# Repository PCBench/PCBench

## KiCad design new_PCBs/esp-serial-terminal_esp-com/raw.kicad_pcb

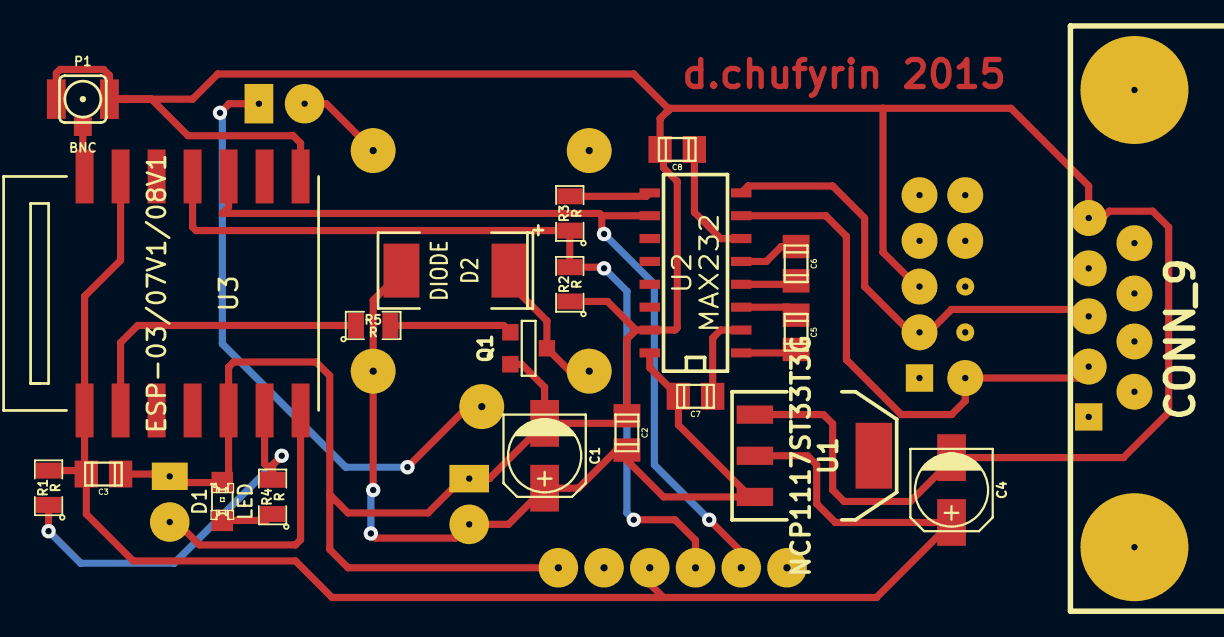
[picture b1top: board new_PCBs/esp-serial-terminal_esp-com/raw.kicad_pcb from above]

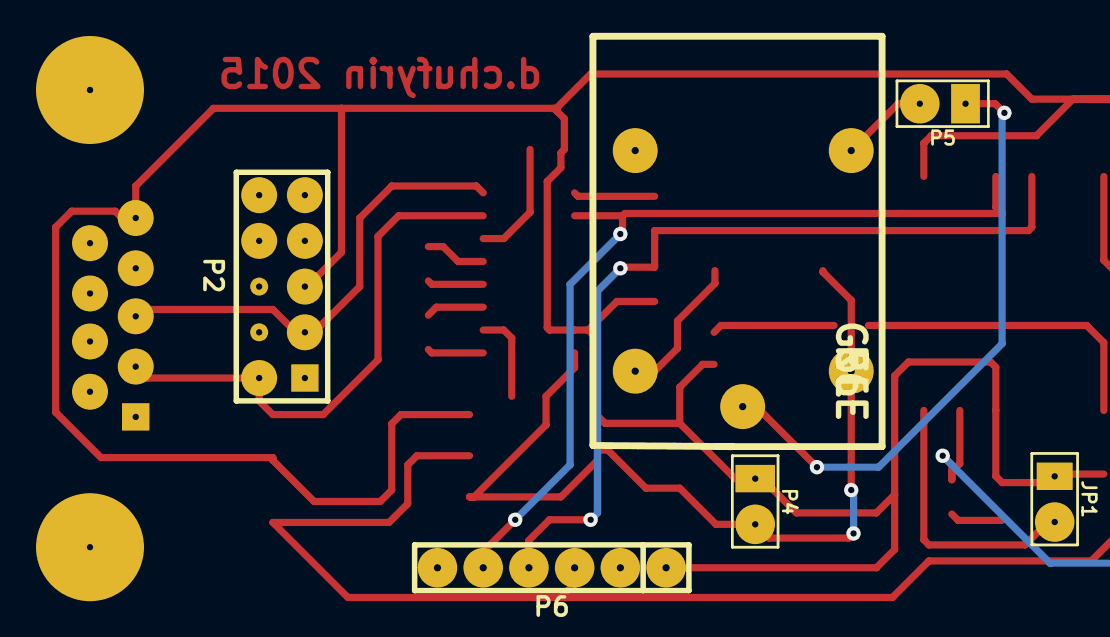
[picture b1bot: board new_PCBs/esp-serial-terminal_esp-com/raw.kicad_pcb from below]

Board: 2 copper layers, 27 parts (6 on the bottom side), 22 nets.

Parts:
C1: CP1; c_elec_4x5.8
C2, C3, C5, C6, C7, C8: C; c_0805
C4: CP1; c_elec_4x5.7
D1: LED; LED-0805
D2: DIODE; SM2512
JP1: JUMPER; PIN_ARRAY_2X1
P1: BNC; coaxial_u.fl-r-smt-1
P2: CONN_5X2; PIN_ARRAY_5x2
P3: CONN_9; DB9MC
P4, P5: CONN_2; PIN_ARRAY_2X1
P6: CONN_6; PIN_ARRAY-6X1
Q1: NPN; SOT23EBC
R1, R2, R3, R4, R5: R; SM0805
R6: G5LE
U1: NCP1117ST33T3G; SOT223
U2: MAX232; SO16E
U3: ESP-03/07V1/08V1; ESP-03

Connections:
+5V: C1.1, C2.1, C7.1, D2.2, P4.2, R6.2, U1.3, U2.16
GND: C1.2, C2.2, C3.2, C4.2, C8.1, D1.2, JP1.1, JP1.2, P1.2, P2.5, P3.5, P4.1, P6.1, Q1.1, R2.1, U1.1, U2.15, U3.5, U3.7, U3.8
unnamed: P2.2, P3.2, U2.7
unnamed: P2.3, P3.3, U2.8
unnamed: D2.1, Q1.3, R6.1
unnamed: C7.2, U2.2
unnamed: C8.2, U2.6
unnamed: C5.2, U2.3
unnamed: C5.1, U2.1
unnamed: C6.1, U2.4
unnamed: C6.2, U2.5
unnamed: R3.2, U2.9
unnamed: P6.4, R2.2, R3.1, U3.11
unnamed: P1.1, U3.14
unnamed: R5.1, U3.2
unnamed: D1.1, R4.1
unnamed: Q1.2, R5.2
unnamed: P5.2, R6.5
unnamed: P5.1, R6.4
unnamed: P6.5, U2.10, U3.10
unnamed: R1.1, R4.2, U3.6
unnamed: C3.1, C4.1, P6.3, R1.2, U1.2, U3.1, U3.13

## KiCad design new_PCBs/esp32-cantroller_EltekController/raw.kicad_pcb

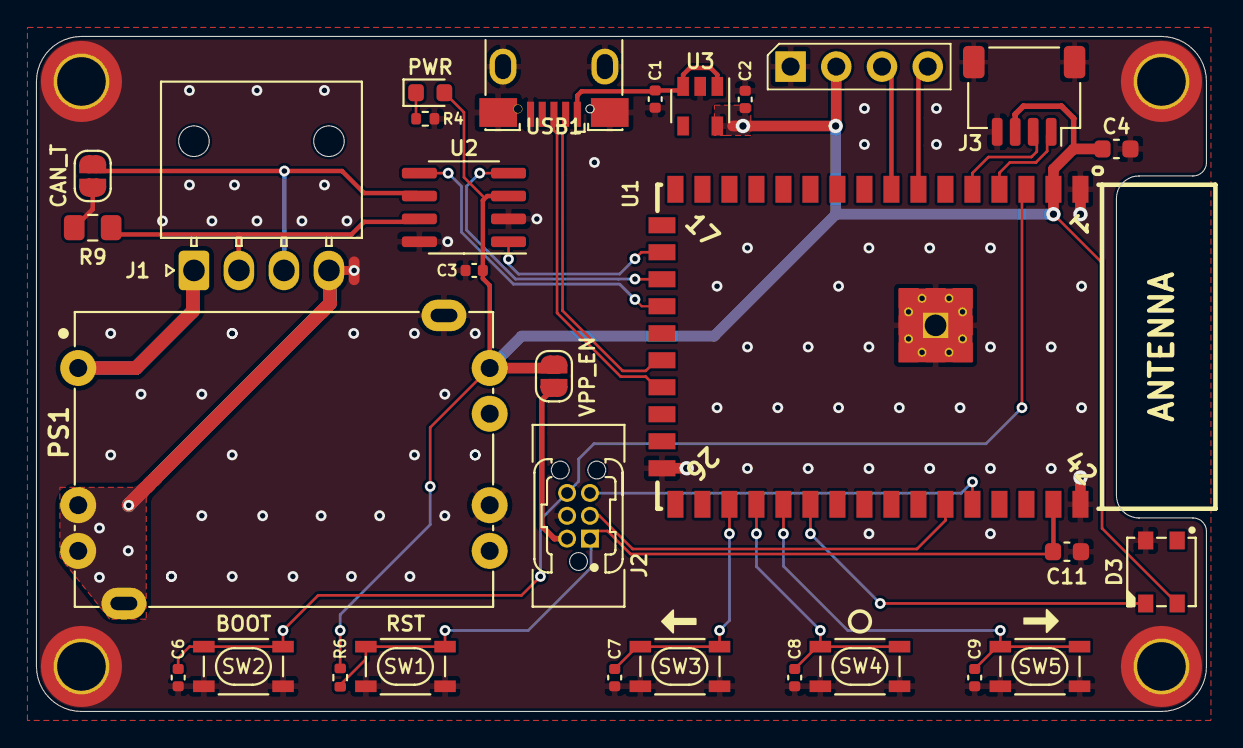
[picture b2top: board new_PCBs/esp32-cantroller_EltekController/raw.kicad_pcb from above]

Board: 2 copper layers, 65.0 x 37.5 mm, 36 parts (1 on the bottom side), 27 nets.

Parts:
C1, C2, C3: 10uF; C_0402_1005Metric
C4: 22uF; C_0603_1608Metric
C6, C7, C8, C9: 100nF; C_0402_1005Metric
C11: 10uF; C_0603_1608Metric
D2: PWR; LED_0603_1608Metric_SnapModel
D3: SK6812MINI; LED_SK6812MINI_PLCC4_3.5x3.5mm_P1.75mm_3D
H1, H2, H3, H4: MP; MountingHole_2.7mm_M2.5_ISO7380_Pad_TopBottom
I2C1: OLED; OLED_SSD1315_128x64_1.3_I2C_New_Silhouette_Big3D
J1: CANBUS; Molex_Nano-Fit_105313-xx04_1x04_P2.50mm_Horizontal_3D
J2: ESP-PROG; Gecko-G125_PlusTC2030_IDCBox_2x03_P1.25mm_Vertical_3D
J3: Qwiic; JST_SH_SM04B-SRSS-TB_1x04-1MP_P1.00mm_Horizontal_3D
JP1: VPP_EN; SolderJumper-2_P1.3mm_Open_RoundedPad1.0x1.5mm
JP2: CAN_T; SolderJumper-2_P1.3mm_Open_RoundedPad1.0x1.5mm
LOGO1: Logo_Open_Hardware_Small; neggle-logo-0.12
NT1: GND_TIE; NetTie-2_SMD_Pad0.5mm
PS1: CC3-4803SF-E; Converter_DCDC_TDK-Lambda_CC3-xxxxxF-E
R4: 1K; R_0402_1005Metric
R6: 10K; R_0402_1005Metric
R9: 120R; R_0805_2012Metric_Pad1.15x1.40mm_HandSolder
SW1: RST; KEY-SMD_4P-L4.2-W3.2-P2.20-LS5.1-TL
SW2: BOOT; KEY-SMD_4P-L4.2-W3.2-P2.20-LS5.1-TL
SW3: LEFT; KEY-SMD_4P-L4.2-W3.2-P2.20-LS5.1-TL
SW4: SEL; KEY-SMD_4P-L4.2-W3.2-P2.20-LS5.1-TL
SW5: RIGHT; KEY-SMD_4P-L4.2-W3.2-P2.20-LS5.1-TL
U1: ESP32-S2-WROVER; ESP32-S2-WROVER_and_WROOM(PCB,-I(IPEX))-Universal
U2: MAX3051ESA; SOIC-8_3.9x4.9mm_P1.27mm
U3: XC6220B331MR; SOT-23-5
USB1: USB; MICRO-USB-SMD_U254-051T-4BH83-F1S_C397452

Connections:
+3V3: C2.2, C3.2, C4.2, D2.2, D3.4, I2C1.2, J3.3, JP1.1, PS1.7, R6.2, U1.2, U2.3, U3.5
+48V: J1.1, PS1.1
/CAN+: J1.2, R9.1, U2.7
/CAN-: J1.3, JP2.2, U2.6
/CAN_RX: U1.19, U2.4
/CAN_TX: U1.18, U2.1
/LED_D: D3.3, U1.32
/OLED_SCL: I2C1.3, U1.8
/OLED_SDA: I2C1.4, U1.7
/QW_SCL: J3.1, U1.4
/QW_SDA: J3.2, U1.5
/U0RXD: J2.5, U1.38
/U0TXD: J2.3, U1.37
/USB_D+: U1.23, USB1.3
/USB_D-: U1.22, USB1.2
/VBUS: C1.2, U3.1, U3.3, USB1.1
/VPP: J2.2, JP1.2
/~BOOT: C6.2, J2.6, SW2.1, U1.3
/~CAN_EN: U1.20, U2.5
/~RST: C11.1, J2.1, R6.1, SW1.1, U1.41
/~SW_L: C7.2, SW3.1, U1.29
/~SW_R: C9.2, SW5.1, U1.31
/~SW_S: C8.2, SW4.1, U1.30
GND: C1.1, C2.1, C3.1, C4.1, C6.1, C7.1, C8.1, C9.1, C11.2, D3.2, H1.1, H2.1, H3.1, H4.1, I2C1.1, J2.4, J3.4, J3.MP, NT1.2, PS1.5, PS1.MP2, R4.1, SW1.2, SW2.2, SW3.2, SW4.2, SW5.2, U1.1, U1.26, U1.42, U1.43, U2.2, U2.8, U3.2, USB1.5, USB1.6
GNDPWR: J1.4, NT1.1, PS1.2, PS1.3, PS1.MP
unnamed: D2.1, R4.2
unnamed: JP2.1, R9.2

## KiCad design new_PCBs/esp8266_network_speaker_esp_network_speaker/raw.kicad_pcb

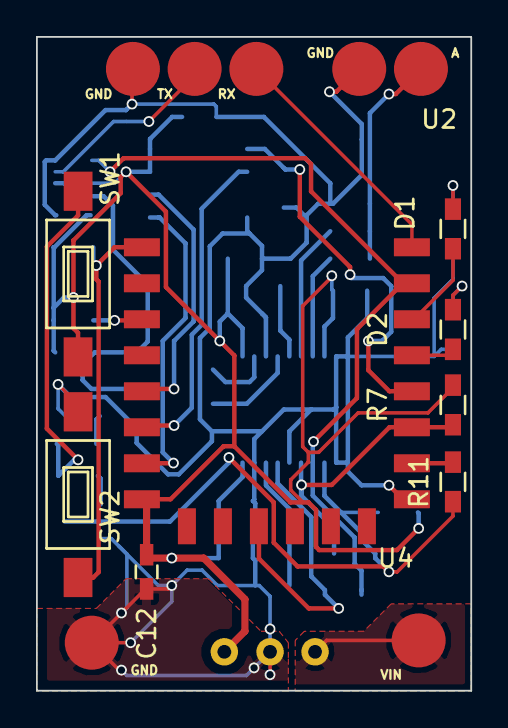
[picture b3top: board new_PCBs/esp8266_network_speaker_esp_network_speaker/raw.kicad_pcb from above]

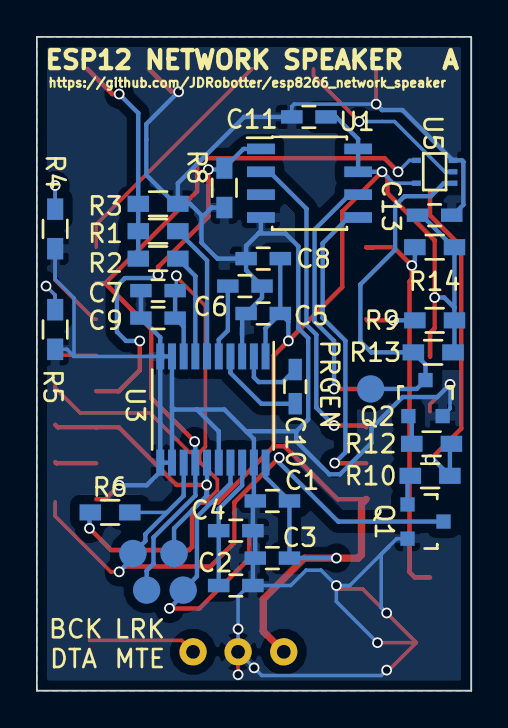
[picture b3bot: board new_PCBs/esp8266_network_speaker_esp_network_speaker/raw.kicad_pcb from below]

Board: 2 copper layers, 24.1 x 36.3 mm, 50 parts (34 on the bottom side), 31 nets.

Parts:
BCK: TEST_1P; Measurement_Point_Round-SMD-Pad_Small
C1, C2, C8, C9, C11, C12, C13: 100nF; C_0603_HandSoldering
C3, C4, C5, C7: 10uF; C_0603_HandSoldering
C6, C10: 2.2uF; C_0603_HandSoldering
D1, D2: LED; R_0603_HandSoldering
DTA: TEST_1P; Measurement_Point_Round-SMD-Pad_Small
LRK: TEST_1P; Measurement_Point_Round-SMD-Pad_Small
MTE: TEST_1P; Measurement_Point_Round-SMD-Pad_Small
PRGEN: TEST_1P; Measurement_Point_Round-SMD-Pad_Small
Q1, Q2: Q_NPN_BEC; SOT-23
R1, R2: 470; R_0603_HandSoldering
R3, R6, R7, R8, R9, R13, R14: 10k; R_0603_HandSoldering
R4, R5: 220; R_0603_HandSoldering
R10, R12: 1k; R_0603_HandSoldering
R11: 100; R_0603_HandSoldering
SW1, SW2: SW_PUSH; SW_SPST_FSMSM
U1: 23LC1024; SOIC-8_3.9x4.9mm_Pitch1.27mm
U2: ESP12
U3: PCM5100A; TSSOP-20_4.4x6.5mm_Pitch0.65mm
U4: TSR_1-2433; TSR-1
U5: M74VHC1GT125; SOT-353
W7: AOUT; Measurement_Point_Round-SMD-Pad_Big
W8: AGND; Measurement_Point_Round-SMD-Pad_Big
W9: PBATT; Measurement_Point_Round-SMD-Pad_Big
W10: PGND; Measurement_Point_Round-SMD-Pad_Big
W11: PROG_GND; Measurement_Point_Round-SMD-Pad_Big
W12: PROG_RX; Measurement_Point_Round-SMD-Pad_Big
W13: PROG_TX; Measurement_Point_Round-SMD-Pad_Big

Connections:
+3V3: C1.1, C3.1, C5.1, C7.1, C8.1, C9.1, C11.1, C12.1, C13.1, R6.1, R7.1, R9.2, R13.1, R14.1, SW1.1, U1.7, U1.8, U2.8, U3.1, U3.8, U3.20, U4.3, U5.5
/PROG_EN: PRGEN.1, Q2.3, R13.2, U5.1
/PROG_TX: U5.2, W13.1
/VBATT: U4.1, W9.1
DAC_BCK: BCK.1, Q1.3, R6.2, R11.1, U3.13
DAC_DATA: DTA.1, U2.21, U3.14, U5.4
DAC_LRCK: LRK.1, R7.2, U2.17, U3.15
DAC_MUTE: MTE.1, U2.11, U3.17
DAC_OUTL: R1.2, U3.6
DAC_OUTR: R2.2, U3.7
ESP12_CLK: U1.6, U2.5
ESP12_CS: R8.1, U1.1, U2.18
ESP12_MISO: U1.2, U2.6
ESP12_MOSI: U1.5, U2.7
ESP12_RESET: R14.2, SW2.1, U2.1
ESP12_TX: U2.22, W12.1
GND: C1.2, C2.1, C3.2, C4.2, C5.2, C6.1, C7.2, C8.2, C9.2, C11.2, C12.2, C13.2, Q1.2, Q2.2, R3.2, R4.1, R5.1, R8.2, SW2.2, U1.4, U2.15, U3.3, U3.9, U3.10, U3.11, U3.12, U3.16, U3.19, U4.2, U5.3, W8.1, W10.1, W11.1
LEDA: D2.2, U2.19
LEDB: D1.2, U2.20
unnamed: C2.2, C4.1, U3.18
unnamed: C6.2, U3.5
unnamed: C10.1, U3.2
unnamed: C10.2, U3.4
unnamed: D1.1, R4.2
unnamed: D2.1, R5.2
unnamed: Q1.1, R10.1
unnamed: Q2.1, R12.1
unnamed: R1.1, R2.1, R3.1, W7.1
unnamed: R9.1, U2.3
unnamed: R10.2, R12.2, SW1.2
unnamed: R11.2, U2.16

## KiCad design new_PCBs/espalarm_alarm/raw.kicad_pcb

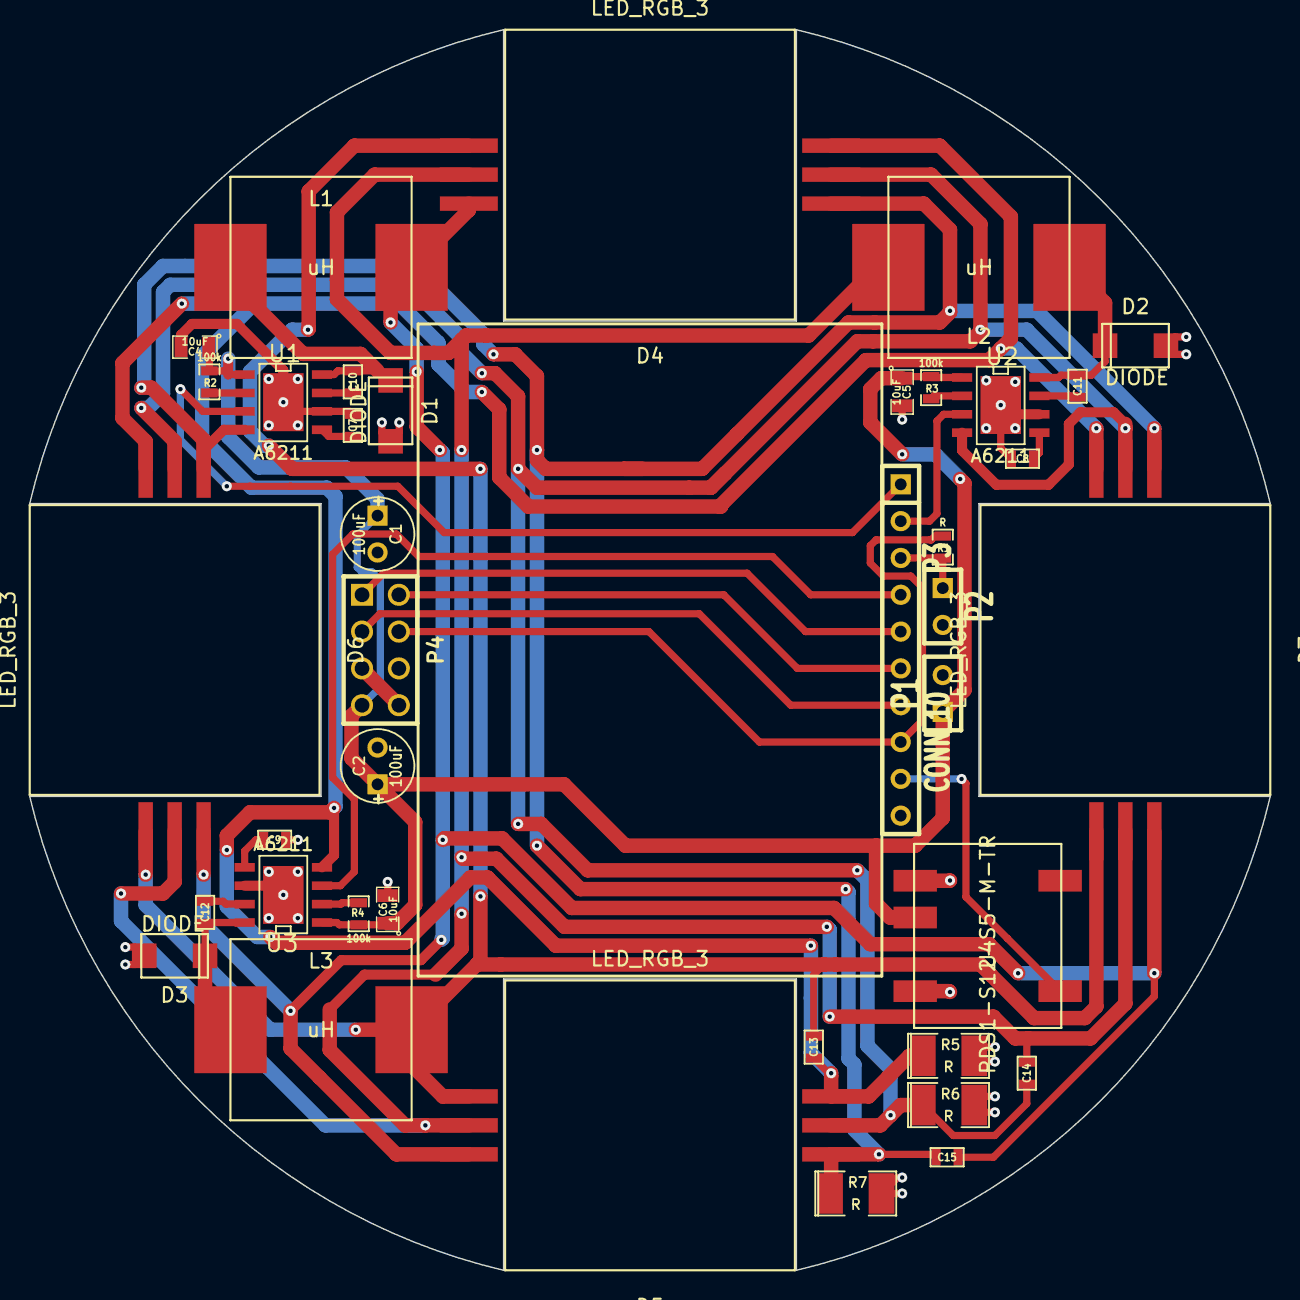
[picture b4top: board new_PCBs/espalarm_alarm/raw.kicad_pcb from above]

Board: 2 copper layers, 85.6 x 85.6 mm, 39 parts (0 on the bottom side), 29 nets.

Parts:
C1, C2: 100uF; C1V5
C4, C5, C6: 10uF; SM0805
C7, C8, C9, C10, C11, C12: 100nF; SM0603
C13, C14, C15: 1uF; SM0603
D1, D2, D3: DIODE; DIODE_SMA
D4, D5, D6, D7: LED_RGB_3; RGB_LED_10W
L1, L2, L3: uH; IND_12.5x12.5mm
P1, P2: CONN_2; SIL-2
P3: CONN_10; SIL-10
P4: CONN_8; pin_array_4x2
R1: R; SM0603_Resistor
R2, R3, R4: 100k; SM0603_Resistor
R5, R6, R7: R; SM1210L
U1, U2, U3: A6211; SO8_WITH_EP
U4: PDS1-S12-S5-M-TR

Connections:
/3.3V: P3.8, P4.4, R1.1
/5V: P3.9, U4.5
/12V: C1.1, C2.1, C4.1, C5.1, C6.1, P1.1, P4.7, R2.1, R3.1, R4.1, U1.1, U2.1, U3.1, U4.2
/GPIO0: P3.7, P4.3
/GPIO2: P3.6, P4.2
/GPIO12: P3.2, U2.3
/GPIO13: P3.4, U3.3
/GPIO14: P3.1, U1.3
/GPIO15: P3.5, P4.1
/GPIO16: P2.1, P3.3, R1.2
GND: C1.2, C2.2, C4.2, C5.2, C6.2, C7.2, C8.2, C9.2, D1.1, D2.1, D3.1, P1.2, P2.2, P3.10, P4.5, P4.8, R5.2, R6.2, R7.2, U1.6, U1.9, U2.6, U2.9, U3.6, U3.9, U4.1, U4.4
unnamed: C14.2, D4.5, D5.5, D6.5, D7.5, R6.1, U2.4
unnamed: C11.1, U2.7
unnamed: C11.2, D2.2, L2.1, U2.8
unnamed: R3.2, U2.2
unnamed: C9.1, U3.5
unnamed: R4.2, U3.2
unnamed: C8.1, U2.5
unnamed: C10.1, U1.7
unnamed: C10.2, D1.2, L1.1, U1.8
unnamed: C12.1, U3.7
unnamed: C12.2, D3.2, L3.1, U3.8
unnamed: C13.1, D4.1, D5.1, D6.1, D7.1, L3.2
unnamed: C7.1, U1.5
unnamed: C15.1, D4.3, D5.3, D6.3, D7.3, L1.2
unnamed: R2.2, U1.2
unnamed: C15.2, D4.4, D5.4, D6.4, D7.4, R7.1, U1.4
unnamed: C13.2, D4.6, D5.6, D6.6, D7.6, R5.1, U3.4
unnamed: C14.1, D4.2, D5.2, D6.2, D7.2, L2.2

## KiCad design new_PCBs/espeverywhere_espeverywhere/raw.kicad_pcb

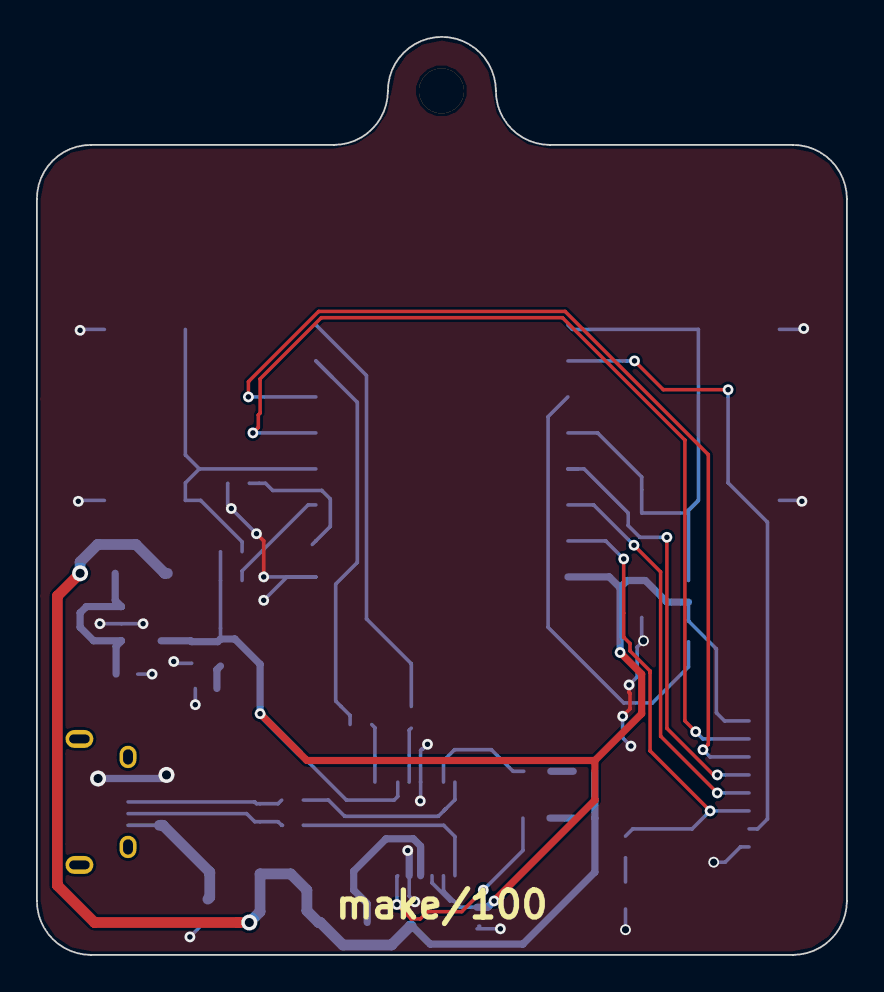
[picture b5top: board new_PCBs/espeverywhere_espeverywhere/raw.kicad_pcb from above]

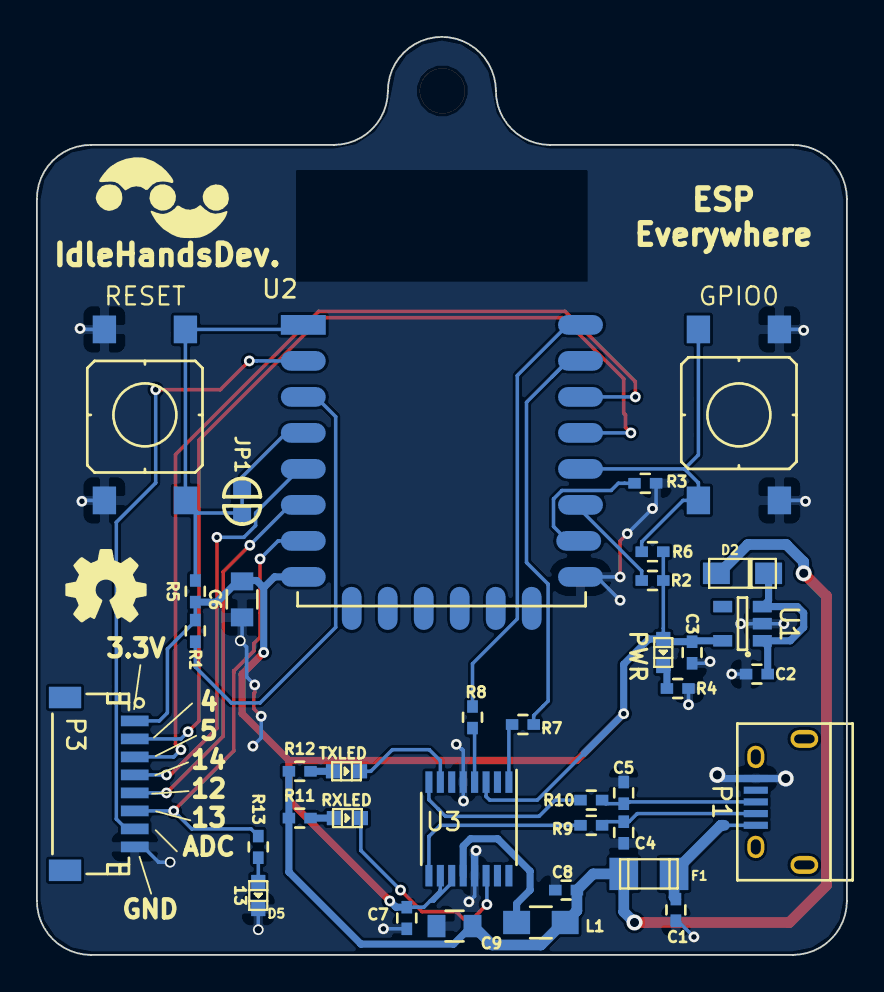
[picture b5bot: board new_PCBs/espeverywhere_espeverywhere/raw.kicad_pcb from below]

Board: 2 copper layers, 45.0 x 51.0 mm, 37 parts (37 on the bottom side), 31 nets.

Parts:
C1, C7, C8: 0.1uF; C_0402_Hand
C2: 1uF; C_0402_Hand
C3: 2.2uF; C_0402_Hand
C4, C5: 47pF; C_0402_Hand
C6, C9: 10uF; C_0805
D1: PWR; Led_0603
D2: BAT20J; bat20j
D3: RXLED; Led_0603
D4: TXLED; Led_0603
D5: 13; Led_0603
F1: 500mA; c_1206
JP1: Jumper_NC_Small; SOLDER-JUMPER_1-WAY-CLOSED
L1: FB; R_0805_HandSoldering
P1: USB_OTG; USB_Micro-B
P3: CONN_01X08; Connectors_JST_SM08B-SRSS-TB
R1, R2, R5: 10K; R_0402_Hand
R3, R4, R6, R7, R8, R11, R12, R13: 1K; R_0402_Hand
R9, R10: 27R; R_0402_Hand
SW2: GPIO0; Button_CKN9112CT-ND
SW3: RESET; Button_CKN9112CT-ND
U1: AP2112K-3.3V; SOT-23-5
U2: ESP-12E; ESP-12E_SMD
U3: FT230XS; SSOP-16_3.9x4.9mm_Pitch0.635mm

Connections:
+3V3: C3.1, C6.2, C7.2, D1.2, P3.1, R1.1, R2.1, R5.1, R6.1, U1.5, U2.8, U3.3, U3.10, U3.11
/ADC: P3.7, U2.2
/CH_PD: R1.2, U2.3
/GPIO0: R6.2, SW2.2, U2.18
/GPIO2: R2.2, U2.17
/GPIO4: P3.2, U2.19
/GPIO5: P3.3, U2.20
/GPIO12: P3.5, U2.6
/GPIO13: P3.6, R13.1, U2.7
/GPIO14: P3.4, U2.5
/GPIO15: R3.1, U2.16
/GPIO16: JP1.1, JP1.2, R5.2, SW3.2, U2.1, U2.4
/RXESP: R7.1, U2.21
/TXESP: R8.1, U2.22
GND: C1.1, C2.2, C3.2, C4.1, C5.1, C6.1, C7.1, C8.1, C9.1, D5.1, P1.5, P3.8, R3.2, R4.2, SW2.1, SW3.1, U1.2, U2.15, U3.5, U3.13
unnamed: C1.2, F1.2, P1.1
unnamed: C2.1, D2.1, U1.1, U1.3
unnamed: C4.2, P1.2, R9.2
unnamed: C5.2, P1.3, R10.2
unnamed: D1.1, R4.1
unnamed: D3.1, U3.14
unnamed: D3.2, R11.2
unnamed: D4.1, U3.7
unnamed: D4.2, R12.2
unnamed: D5.2, R13.2
unnamed: L1.1, U3.12
unnamed: R7.2, U3.1
unnamed: R8.2, U3.4
unnamed: R9.1, U3.9
unnamed: R10.1, U3.8
VUSB: C8.2, C9.2, D2.2, F1.1, L1.2, R11.1, R12.1

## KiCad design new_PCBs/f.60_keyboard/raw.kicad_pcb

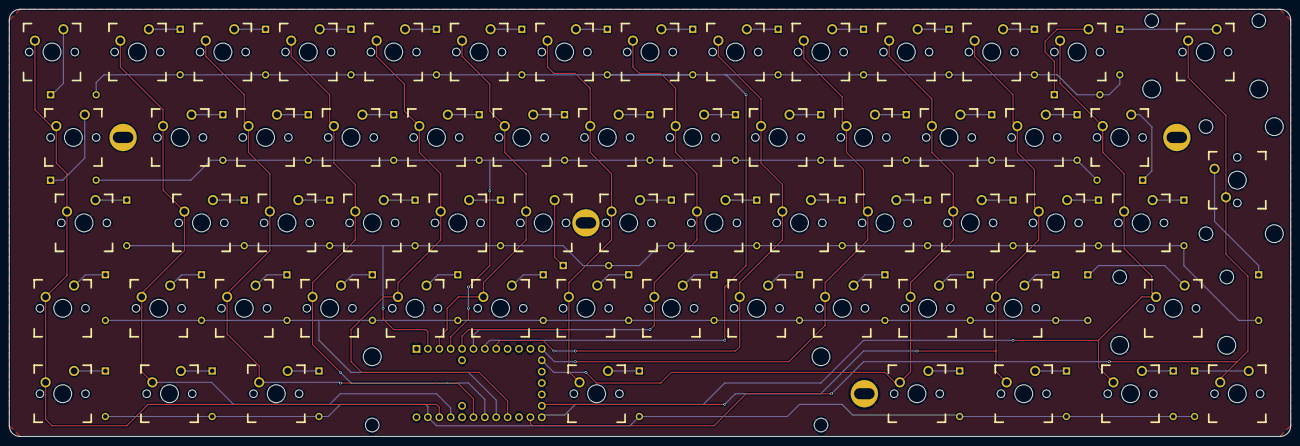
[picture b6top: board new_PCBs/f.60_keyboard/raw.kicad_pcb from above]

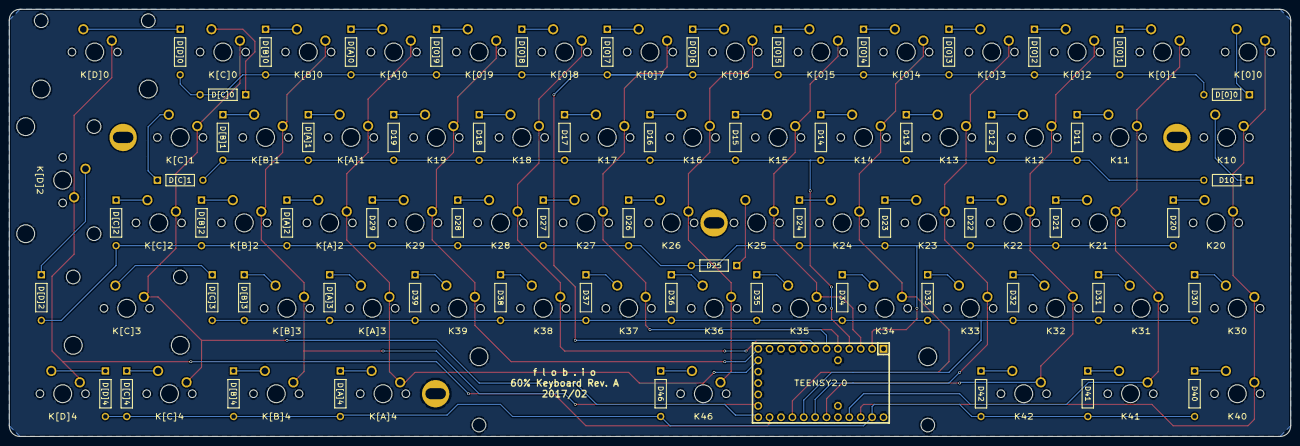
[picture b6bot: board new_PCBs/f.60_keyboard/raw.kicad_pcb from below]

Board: 2 copper layers, 285.8 x 95.3 mm, 129 parts (63 on the bottom side), 81 nets.

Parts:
D10, D11, D12, D13, D14, D15, D16, D17, D18, D19, D20, D21, D22, D23, D24, D25, D26, D27, D28, D29, D30, D31, D32, D33, D34, D35, D36, D37, D38, D39, D40, D41, D42, D46: D; DIODE
D[0]0, D[0]1, D[0]2, D[0]3, D[0]4, D[0]5, D[0]6, D[0]7, D[0]8, D[0]9: D; DIODE
D[A]0, D[A]1, D[A]2, D[A]3, D[A]4: D; DIODE
D[B]0, D[B]1, D[B]2, D[B]3, D[B]4: D; DIODE
D[C]0, D[C]1, D[C]2, D[C]3, D[C]4: D; DIODE
D[D]0, D[D]2, D[D]4: D; DIODE
K10: Tab; CHERRY_PCB_150H
K11: Q; CHERRY_PCB_100H
K12: W; CHERRY_PCB_100H
K13: E; CHERRY_PCB_100H
K14: R; CHERRY_PCB_100H
K15: T; CHERRY_PCB_100H
K16: Y; CHERRY_PCB_100H
K17: U; CHERRY_PCB_100H
K18: I; CHERRY_PCB_100H
K19: O; CHERRY_PCB_100H
K20: CapsLock; CHERRY_PCB_175H
K21: A; CHERRY_PCB_100H
K22: S; CHERRY_PCB_100H
K23: D; CHERRY_PCB_100H
K24: F; CHERRY_PCB_100H
K25: G; CHERRY_PCB_100H
K26: H; CHERRY_PCB_100H
K27: J; CHERRY_PCB_100H
K28: K; CHERRY_PCB_100H
K29: L; CHERRY_PCB_100H
K30: LShift; CHERRY_PCB_125H
K31: \; CHERRY_PCB_100H
K32: Z; CHERRY_PCB_100H
K33: X; CHERRY_PCB_100H
K34: C; CHERRY_PCB_100H
K35: V; CHERRY_PCB_100H
K36: B; CHERRY_PCB_100H
K37: N; CHERRY_PCB_100H
K38: M; CHERRY_PCB_100H
K39: ,; CHERRY_PCB_100H
K40: LCtrl; CHERRY_PCB_125H
K41: LSuper; CHERRY_PCB_125H
K42: LAlt; CHERRY_PCB_125H
K46: Space; CHERRY_PCB_625H
K[0]0: Esc; CHERRY_PCB_100H
K[0]1: 1; CHERRY_PCB_100H
K[0]2: 2; CHERRY_PCB_100H
K[0]3: 3; CHERRY_PCB_100H
K[0]4: 4; CHERRY_PCB_100H
K[0]5: 5; CHERRY_PCB_100H
K[0]6: 6; CHERRY_PCB_100H
K[0]7: 7; CHERRY_PCB_100H
K[0]8: 8; CHERRY_PCB_100H
K[0]9: 9; CHERRY_PCB_100H
K[A]0: 0; CHERRY_PCB_100H
K[A]1: P; CHERRY_PCB_100H
K[A]2: ;; CHERRY_PCB_100H
K[A]3: .; CHERRY_PCB_100H
K[A]4: RAltGr; CHERRY_PCB_125H
K[B]0: -; CHERRY_PCB_100H
K[B]1: [; CHERRY_PCB_100H
K[B]2: '; CHERRY_PCB_100H
K[B]3: /; CHERRY_PCB_100H
K[B]4: RSuper; CHERRY_PCB_125H
K[C]0: =; CHERRY_PCB_100H
K[C]1: ]; CHERRY_PCB_100H
K[C]2: #; CHERRY_PCB_100H
K[C]3: RShift; CHERRY_PCB_275H
K[C]4: Menu; CHERRY_PCB_125H
K[D]0: Backspace; CHERRY_PCB_200H
K[D]2: Enter; CHERRY_PCB_ISOR
K[D]4: RCtrl; CHERRY_PCB_125H
MH1, MH2, MH3, MH4: Poker_oval_hole
U1: TEENSY2.0; Teensy_20

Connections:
/C0: K10.2, K20.2, K30.2, K40.2, K[0]0.2, U1.27
/C1: K11.2, K21.2, K31.2, K41.2, K[0]1.2, U1.26
/C2: K12.2, K22.2, K32.2, K42.2, K[0]2.2, U1.24
/C3: K13.2, K23.2, K33.2, K[0]3.2, U1.23
/C4: K14.2, K24.2, K34.2, K[0]4.2, U1.21
/C5: K15.2, K25.2, K35.2, K[0]5.2, U1.3
/C6: K16.2, K26.2, K36.2, K46.2, K[0]6.2, U1.5
/C7: K17.2, K27.2, K37.2, K[0]7.2, U1.6
/C8: K18.2, K28.2, K38.2, K[0]8.2, U1.8
/C9: K19.2, K29.2, K39.2, K[0]9.2, U1.12
/C10: K[A]0.2, K[A]1.2, K[A]2.2, K[A]3.2, K[A]4.2, U1.13
/C11: K[B]0.2, K[B]1.2, K[B]2.2, K[B]3.2, K[B]4.2, U1.17
/C12: K[C]0.2, K[C]1.2, K[C]2.2, K[C]3.2, K[C]4.2, U1.18
/C13: K[D]0.2, K[D]2.2, K[D]4.2, U1.19
/R0: D[0]0.1, D[0]1.1, D[0]2.1, D[0]3.1, D[0]4.1, D[0]5.1, D[0]6.1, D[0]7.1, D[0]8.1, D[0]9.1, D[A]0.1, D[B]0.1, D[C]0.1, D[D]0.1, U1.7
/R1: D10.1, D11.1, D12.1, D13.1, D14.1, D15.1, D16.1, D17.1, D18.1, D19.1, D[A]1.1, D[B]1.1, D[C]1.1, U1.4
/R2: D20.1, D21.1, D22.1, D23.1, D24.1, D25.1, D26.1, D27.1, D28.1, D29.1, D[A]2.1, D[B]2.1, D[C]2.1, D[D]2.1, U1.2
/R3: D30.1, D31.1, D32.1, D33.1, D34.1, D35.1, D36.1, D37.1, D38.1, D39.1, D[A]3.1, D[B]3.1, D[C]3.1, U1.22
/R4: D40.1, D41.1, D42.1, D46.1, D[A]4.1, D[B]4.1, D[C]4.1, D[D]4.1, U1.28
unnamed: D10.2, K10.1
unnamed: D11.2, K11.1
unnamed: D12.2, K12.1
unnamed: D13.2, K13.1
unnamed: D14.2, K14.1
unnamed: D15.2, K15.1
unnamed: D16.2, K16.1
unnamed: D17.2, K17.1
unnamed: D18.2, K18.1
unnamed: D19.2, K19.1
unnamed: D20.2, K20.1
unnamed: D21.2, K21.1
unnamed: D22.2, K22.1
unnamed: D23.2, K23.1
unnamed: D24.2, K24.1
unnamed: D25.2, K25.1
unnamed: D26.2, K26.1
unnamed: D27.2, K27.1
unnamed: D28.2, K28.1
unnamed: D29.2, K29.1
unnamed: D30.2, K30.1
unnamed: D31.2, K31.1
unnamed: D32.2, K32.1
unnamed: D33.2, K33.1
unnamed: D34.2, K34.1
unnamed: D35.2, K35.1
unnamed: D36.2, K36.1
unnamed: D37.2, K37.1
unnamed: D38.2, K38.1
unnamed: D39.2, K39.1
unnamed: D40.2, K40.1
unnamed: D41.2, K41.1
unnamed: D42.2, K42.1
unnamed: D46.2, K46.1
unnamed: D[0]0.2, K[0]0.1
unnamed: D[0]1.2, K[0]1.1
unnamed: D[0]2.2, K[0]2.1
unnamed: D[0]3.2, K[0]3.1
unnamed: D[0]4.2, K[0]4.1
unnamed: D[0]5.2, K[0]5.1
unnamed: D[0]6.2, K[0]6.1
unnamed: D[0]7.2, K[0]7.1
unnamed: D[0]8.2, K[0]8.1
unnamed: D[0]9.2, K[0]9.1
unnamed: D[A]0.2, K[A]0.1
unnamed: D[A]1.2, K[A]1.1
unnamed: D[A]2.2, K[A]2.1
unnamed: D[A]3.2, K[A]3.1
unnamed: D[A]4.2, K[A]4.1
unnamed: D[B]0.2, K[B]0.1
unnamed: D[B]1.2, K[B]1.1
unnamed: D[B]2.2, K[B]2.1
unnamed: D[B]3.2, K[B]3.1
unnamed: D[B]4.2, K[B]4.1
unnamed: D[C]0.2, K[C]0.1
unnamed: D[C]1.2, K[C]1.1
unnamed: D[C]2.2, K[C]2.1
unnamed: D[C]3.2, K[C]3.1
unnamed: D[C]4.2, K[C]4.1
unnamed: D[D]0.2, K[D]0.1
unnamed: D[D]2.2, K[D]2.1
unnamed: D[D]4.2, K[D]4.1
